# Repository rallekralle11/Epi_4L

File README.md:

# Epi
# This thing is about to get launched on Crowd Supply

Named after the Epipactis genus of orchids. The flower of one appears on the board.

Data sheet: https://ping-el.se/wp-content/uploads/2023/10/datasheet.pdf
Kicad footprints: https://github.com/rallekralle11/kicad-lib

With such "amazing" features as:

USB power and data line ESD protection as well as power filtration and a fuse.

Crenellated pins.

No integrated voltage converter, only runs at 4,5-5,5v(down to 2,7 if you make it with an 8mhz crystal, or use the internal oscillator).

USB-C connector sunk into the board, and slighly portruding from the end for panel mounting.

1,27mm pin spacing.

Extra pins broken out.

Holes where M2 bolts can be used to hold it in place.

No rx/tx/power LEDs. Only one on pin 13 for testing.

Includes some custom footprints with 3D models.

Size comparisons.

Licensed under CERN-OHL-P v2

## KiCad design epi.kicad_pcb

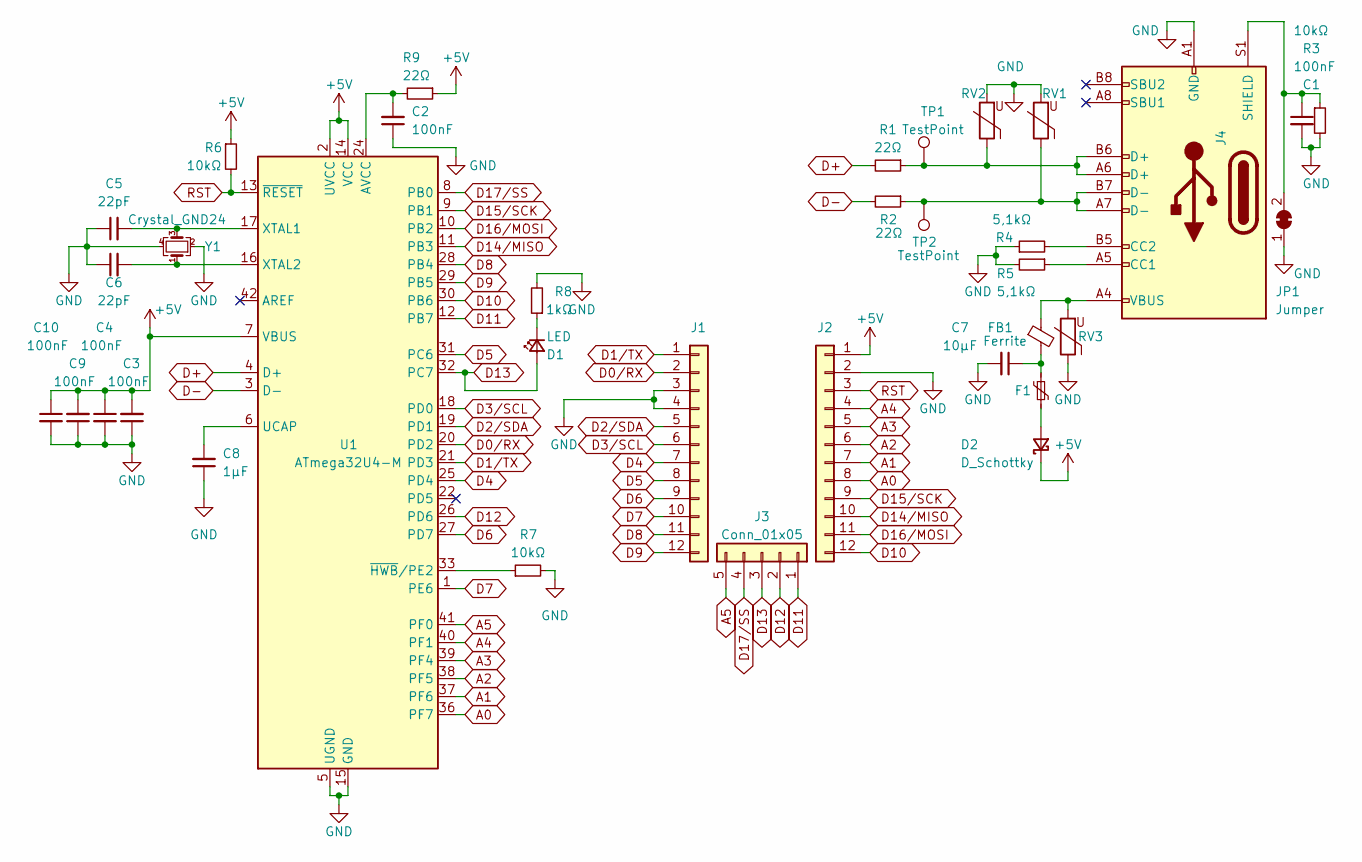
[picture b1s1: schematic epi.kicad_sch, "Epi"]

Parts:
C1, C2, C3, C4, C9, C10: 100nF; R_0402_1005Metric
C5, C6: 22pF; R_0402_1005Metric
C7: 10µF; R_0402_1005Metric
C8: 1µF; R_0402_1005Metric
D1: LED; LED_0402_1005Metric
D2: D_Schottky; SOD323_bättre
F1: Polyfuse 500mA HC; R_0402_1005Metric
FB1: Ferrite; R_0402_1005Metric
J1, J2: Connector 1x12; PinHeader_1x12_P1.27mm_Vertical
J3: Conn_01x05; PinHeader_1x05_P1.27mm_Vertical
J4: USB-C 2.0 mid-mount female connector; USB-C MC-314C-4P16
JP1: Jumper; SolderJumper-2_P1.3mm_Bridged_RoundedPad1.0x1.5mm
R1, R2, R9: 22Ω; R_0402_1005Metric
R3, R6, R7: 10kΩ; R_0402_1005Metric
R4, R5: 5,1kΩ; R_0402_1005Metric
R8: 1kΩ; R_0402_1005Metric
RV1, RV2, RV3: ESD protection varistor; R_0402_1005Metric
TP1, TP2: TestPoint; TestPoint_Pad_D1.0mm
U1: ATmega32U4-M; QFN-44-1EP_7x7mm_P0.5mm_EP5.2x5.2mm
Y1: Crystal_GND24; Crystal_SMD_2016-4Pin_2.0x1.6mm

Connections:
+5V: C3.2, C4.1, C9.2, C10.1, D2.1 (K), J2.1, R6.1, R9.1, U1.2 (UVCC), U1.7 (VBUS), U1.14 (VCC), U1.34 (VCC)
A0: J2.8, U1.36 (PF7)
A1: J2.7, U1.37 (PF6)
A2: J2.6, U1.38 (PF5)
A3: J2.5, U1.39 (PF4)
A4: J2.4, U1.40 (PF1)
A5: J3.5, U1.41 (PF0)
D0/RX: J1.2, U1.20 (PD2)
D1/TX: J1.1, U1.21 (PD3)
D2/SDA: J1.5, U1.19 (PD1)
D3/SCL: J1.6, U1.18 (PD0)
D4: J1.7, U1.25 (PD4)
D5: J1.8, U1.31 (PC6)
D6: J1.9, U1.27 (PD7)
D7: J1.10, U1.1 (PE6)
D8: J1.11, U1.28 (PB4)
D9: J1.12, U1.29 (PB5)
D10: J2.12, U1.30 (PB6)
D11: J3.1, U1.12 (PB7)
D12: J3.2, U1.26 (PD6)
D13: D1.2 (A), J3.3, U1.32 (PC7)
D14/MISO: J2.10, U1.11 (PB3)
D15/SCK: J2.9, U1.9 (PB1)
D16/MOSI: J2.11, U1.10 (PB2)
D17/SS: J3.4, U1.8 (PB0)
D+: R1.2, U1.4 (D+)
D-: R2.2, U1.3 (D-)
GND: C1.2, C2.1, C3.1, C4.2, C5.1, C6.1, C7.2, C8.1, C9.1, C10.2, J1.3, J1.4, J2.2, J4.A1 (GND), J4.A12 (GND), J4.B1 (GND), J4.B12 (GND), JP1.1 (A), R3.2, R4.1, R5.2, R7.2, R8.2, RV1.2, RV2.2, RV3.1, U1.5 (UGND), U1.15 (GND), U1.23 (GND), U1.35 (GND), U1.43 (GND), U1.45 (GND), Y1.2, Y1.4
unnamed: C2.2, R9.2, U1.24 (AVCC), U1.44 (AVCC)
unnamed: C7.1, F1.1, FB1.2
unnamed: D1.1 (K), R8.1
unnamed: D2.2 (A), F1.2
unnamed: FB1.1, J4.A4 (VBUS), J4.A9 (VBUS), J4.B4 (VBUS), J4.B9 (VBUS), RV3.2
unnamed: J4.A5 (CC1), R5.1
unnamed: J4.B5 (CC2), R4.2
unnamed: J4.A6 (D+), J4.B6 (D+), R1.1, RV2.1, TP1.1
unnamed: J4.A7 (D-), J4.B7 (D-), R2.1, RV1.1, TP2.1
unnamed: C1.1, J4.S1 (SHIELD), JP1.2 (B), R3.1
unnamed: C8.2, U1.6 (UCAP)
unnamed: C5.2, U1.17 (XTAL1), Y1.3
unnamed: C6.2, U1.16 (XTAL2), Y1.1
unnamed: R7.1, U1.33 (~HWB/PE2)
RST: J2.3, R6.2, U1.13 (~RESET)

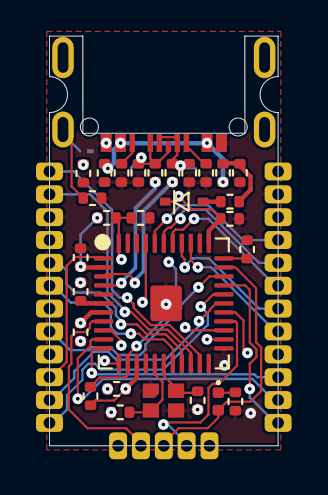
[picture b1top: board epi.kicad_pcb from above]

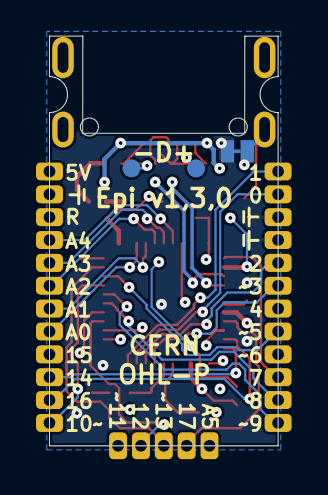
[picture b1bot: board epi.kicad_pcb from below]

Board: 4 copper layers, 12.7 x 22.8 mm, 37 parts (3 on the bottom side), 43 nets.

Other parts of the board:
DRILL1, DRILL2: NPTH

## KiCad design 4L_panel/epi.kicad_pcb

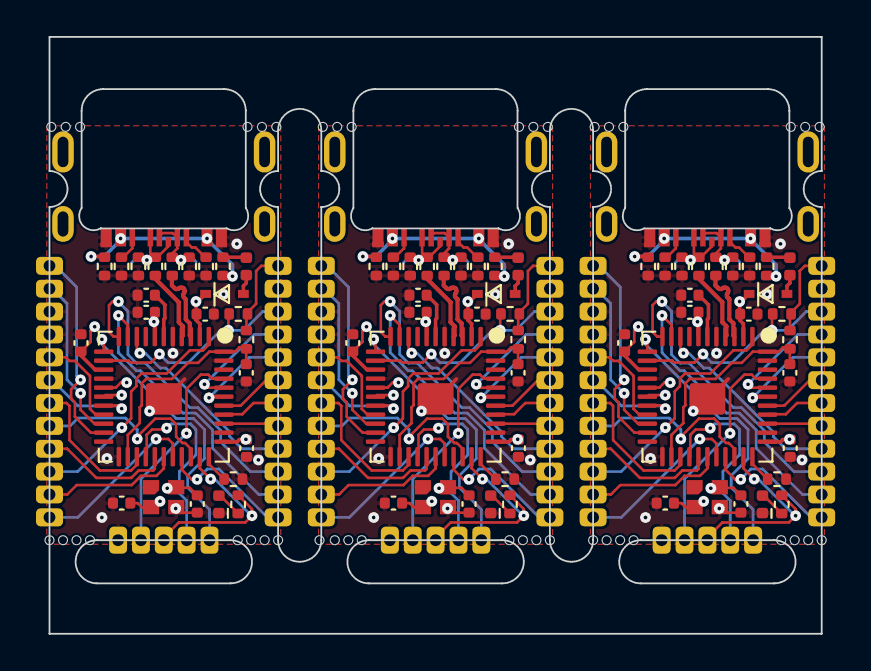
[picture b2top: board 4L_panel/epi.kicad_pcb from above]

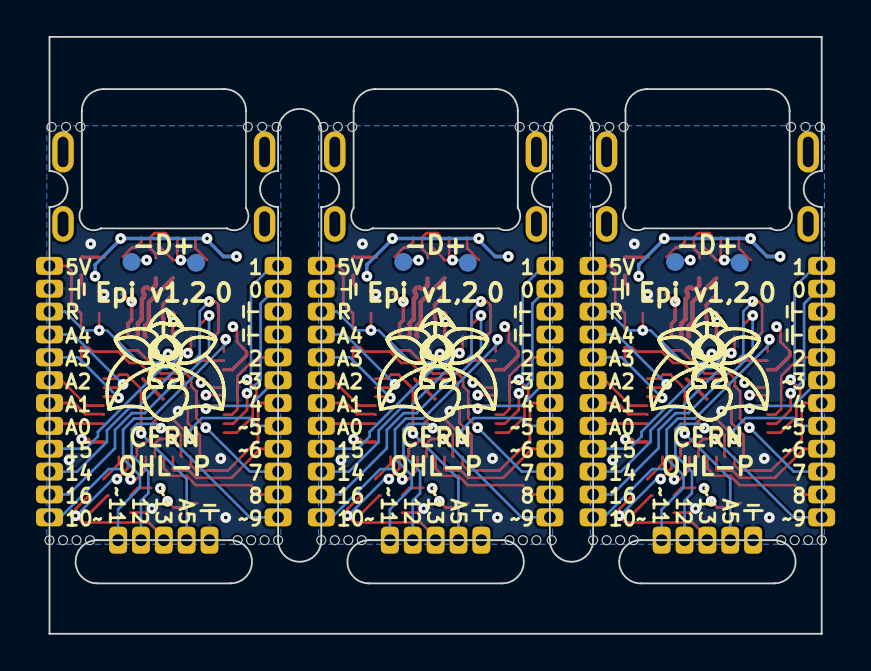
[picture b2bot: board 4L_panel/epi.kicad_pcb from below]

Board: 4 copper layers, 42.9 x 33.2 mm, 93 parts (6 on the bottom side), 41 nets.

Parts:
C2, C3, C4, C7, C9, C10, C11, C12, C16, C17, C18, C19, C20, C24, C25: 100nF; C_0402_1005Metric
C5, C6, C13, C14, C21, C22: 22pF; C_0402_1005Metric
C8, C15, C23: 1µF; C_0402_1005Metric
D1, D3, D5: LED; LED_0402_1005Metric
D2, D4, D6: D_Schottky; SOD323_bättre
F1, F2, F3: Polyfuse 500mA HC; Fuse_0402_1005Metric
FB1, FB2, FB3: Ferrite; R_0402_1005Metric
J1, J2, J5, J6, J9, J10: Connector 1x12; PinHeader_1x12_P1.27mm_Vertical
J3, J7, J11: Conn_01x05; PinHeader_1x05_P1.27mm_Vertical
J4, J8, J12: USB-C 2.0 mid-mount female connector; USB-C MC-314C-4P16
R1, R2, R3, R9, R10, R16, R17, R18, R24: 22Ω; R_0402_1005Metric
R4, R5, R11, R12, R19, R20: 5,1kΩ; R_0402_1005Metric
R6, R7, R13, R14, R21, R22: 10kΩ; R_0402_1005Metric
R8, R15, R23: 1kΩ; R_0402_1005Metric
RV1, RV2, RV3, RV4, RV5, RV6, RV7, RV8, RV9: ESD protection varistor; R_0402_1005Metric
TP1, TP2, TP3, TP4, TP5, TP6: TestPoint; TestPoint_Pad_D1.0mm
U1, U2, U3: ATmega32U4-M; QFN-44-1EP_7x7mm_P0.5mm_EP5.2x5.2mm
Y1, Y2, Y3: Crystal_GND24; Crystal_SMD_2016-4Pin_2.0x1.6mm

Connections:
+5V: C3.2, C4.1, C9.2, C10.1, C11.2, C12.1, C16.2, C17.1, C19.2, C20.1, C24.2, C25.1, D2.1 (K), D4.1 (K), D6.1 (K), J2.1, J6.1, J10.1, R6.1, R9.1, R13.1, R16.1, R21.1, R24.1, U1.2 (UVCC), U1.7 (VBUS), U1.14 (VCC), U1.34 (VCC), U2.2 (UVCC), U2.7 (VBUS), U2.14 (VCC), U2.34 (VCC), U3.2 (UVCC), U3.7 (VBUS), U3.14 (VCC), U3.34 (VCC)
A0: J2.8, J6.8, J10.8, U1.36 (PF7), U2.36 (PF7), U3.36 (PF7)
A1: J2.7, J6.7, J10.7, U1.37 (PF6), U2.37 (PF6), U3.37 (PF6)
A2: J2.6, J6.6, J10.6, U1.38 (PF5), U2.38 (PF5), U3.38 (PF5)
A3: J2.5, J6.5, J10.5, U1.39 (PF4), U2.39 (PF4), U3.39 (PF4)
A4: J2.4, J6.4, J10.4, U1.40 (PF1), U2.40 (PF1), U3.40 (PF1)
A5: J3.4, J7.4, J11.4, U1.41 (PF0), U2.41 (PF0), U3.41 (PF0)
D0/RX: J1.2, J5.2, J9.2, U1.20 (PD2), U2.20 (PD2), U3.20 (PD2)
D1/TX: J1.1, J5.1, J9.1, U1.21 (PD3), U2.21 (PD3), U3.21 (PD3)
D2/SDA: J1.5, J5.5, J9.5, U1.19 (PD1), U2.19 (PD1), U3.19 (PD1)
D3/SCL: J1.6, J5.6, J9.6, U1.18 (PD0), U2.18 (PD0), U3.18 (PD0)
D4: J1.7, J5.7, J9.7, U1.25 (PD4), U2.25 (PD4), U3.25 (PD4)
D5: J1.8, J5.8, J9.8, U1.31 (PC6), U2.31 (PC6), U3.31 (PC6)
D6: J1.9, J5.9, J9.9, U1.27 (PD7), U2.27 (PD7), U3.27 (PD7)
D7: J1.10, J5.10, J9.10, U1.1 (PE6), U2.1 (PE6), U3.1 (PE6)
D8: J1.11, J5.11, J9.11, U1.28 (PB4), U2.28 (PB4), U3.28 (PB4)
D9: J1.12, J5.12, J9.12, U1.29 (PB5), U2.29 (PB5), U3.29 (PB5)
D10: J2.12, J6.12, J10.12, U1.30 (PB6), U2.30 (PB6), U3.30 (PB6)
D11: J3.1, J7.1, J11.1, U1.12 (PB7), U2.12 (PB7), U3.12 (PB7)
D12: J3.2, J7.2, J11.2, U1.26 (PD6), U2.26 (PD6), U3.26 (PD6)
D13: J3.3, J7.3, J11.3, R8.1, R15.1, R23.1, U1.32 (PC7), U2.32 (PC7), U3.32 (PC7)
D14/MISO: J2.10, J6.10, J10.10, U1.11 (PB3), U2.11 (PB3), U3.11 (PB3)
D15/SCK: J2.9, J6.9, J10.9, U1.9 (PB1), U2.9 (PB1), U3.9 (PB1)
D16/MOSI: J2.11, J6.11, J10.11, U1.10 (PB2), U2.10 (PB2), U3.10 (PB2)
D+: R1.2, R3.2, R17.2, U1.4 (D+), U2.4 (D+), U3.4 (D+)
D-: R2.2, R10.2, R18.2, U1.3 (D-), U2.3 (D-), U3.3 (D-)
GND: C2.1, C3.1, C4.2, C5.1, C6.1, C7.1, C8.1, C9.1, C10.2, C11.1, C12.2, C13.1, C14.1, C15.1, C16.1, C17.2, C18.1, C19.1, C20.2, C21.1, C22.1, C23.1, C24.1, C25.2, D1.1 (K), D3.1 (K), D5.1 (K), J1.3, J1.4, J2.2, J3.5, J4.A1 (GND), J4.B12 (GND), J5.3, J5.4, J6.2, J7.5, J8.A1 (GND), J8.B12 (GND), J9.3, J9.4, J10.2, J11.5, J12.A1 (GND), J12.B12 (GND), R4.1, R5.2, R7.2, R11.1, R12.2, R14.2, R19.1, R20.2, R22.2, RV1.2, RV2.2, RV3.1, RV4.2, RV5.2, RV6.1, RV7.2, RV8.2, RV9.1, U1.5 (UGND), U1.15 (GND), U1.23 (GND), U1.35 (GND), U1.43 (GND), U1.45 (GND), U2.5 (UGND), U2.15 (GND), U2.23 (GND), U2.35 (GND), U2.43 (GND), U2.45 (GND), U3.5 (UGND), U3.15 (GND), U3.23 (GND), U3.35 (GND), U3.43 (GND), U3.45 (GND), Y1.2, Y1.4, Y2.2, Y2.4, Y3.2, Y3.4
unnamed: C2.2, C7.2, C18.2, R9.2, R16.2, R24.2, U1.24 (AVCC), U1.44 (AVCC), U2.24 (AVCC), U2.44 (AVCC), U3.24 (AVCC), U3.44 (AVCC)
unnamed: C5.2, C13.2, C21.2, U1.17 (XTAL1), U2.17 (XTAL1), U3.17 (XTAL1), Y1.3, Y2.3, Y3.3
unnamed: C6.2, C14.2, C22.2, U1.16 (XTAL2), U2.16 (XTAL2), U3.16 (XTAL2), Y1.1, Y2.1, Y3.1
unnamed: C8.2, C15.2, C23.2, U1.6 (UCAP), U2.6 (UCAP), U3.6 (UCAP)
unnamed: D1.2 (A), D3.2 (A), D5.2 (A), R8.2, R15.2, R23.2
unnamed: D2.2 (A), D4.2 (A), D6.2 (A), F1.2, F2.2, F3.2
unnamed: F1.1, F2.1, F3.1, FB1.2, FB2.2, FB3.2
unnamed: FB1.1, FB2.1, FB3.1, J4.A4 (VBUS), J4.A9 (VBUS), J8.A4 (VBUS), J8.A9 (VBUS), J12.A4 (VBUS), J12.A9 (VBUS), RV3.2, RV6.2, RV9.2
unnamed: J4.A5 (CC1), J8.A5 (CC1), J12.A5 (CC1), R5.1, R12.1, R20.1
unnamed: J4.A6 (D+), J4.B6 (D+), J8.A6 (D+), J8.B6 (D+), J12.A6 (D+), J12.B6 (D+), R1.1, R3.1, R17.1, RV2.1, RV5.1, RV8.1, TP1.1, TP3.1, TP5.1
unnamed: J4.A7 (D-), J4.B7 (D-), J8.A7 (D-), J8.B7 (D-), J12.A7 (D-), J12.B7 (D-), R2.1, R10.1, R18.1, RV1.1, RV4.1, RV7.1, TP2.1, TP4.1, TP6.1
unnamed: J4.B5 (CC2), J8.B5 (CC2), J12.B5 (CC2), R4.2, R11.2, R19.2
unnamed: R7.1, R14.1, R22.1, U1.33 (~HWB/PE2), U2.33 (~HWB/PE2), U3.33 (~HWB/PE2)
RST: J2.3, J6.3, J10.3, R6.2, R13.2, R21.2, U1.13 (~RESET), U2.13 (~RESET), U3.13 (~RESET)

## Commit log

2023-01-04 initial
2023-01-07 pictures!
2023-01-07 minor changes
2023-01-21 minor design changes and pinout diagram added
2023-01-21 improved pinout colours for git
2023-01-21 comparison update
2023-01-22 removed broken files
2023-02-04 added gerbers
2023-06-08 new computer, new updates
2023-06-08 gerbers update
2023-06-09 gerbers and pictures
2023-07-20 slight edge cuts change
2023-07-20 messing with outline and also spark gap
2023-07-22 changed the method for inset corners to make space for the USB port
2023-07-23 USB shield connection set up
2023-07-23 guess it needs a new BOM as well
2023-09-09 big redesign
2023-09-19 little fix and updated gerbers
2023-10-14 bit of everything
